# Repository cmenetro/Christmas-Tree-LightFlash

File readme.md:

Christmas Tree Light Flash
===

The way to blink a christmas light who is powered on batteries.
For blink I use a 555 timer chip.

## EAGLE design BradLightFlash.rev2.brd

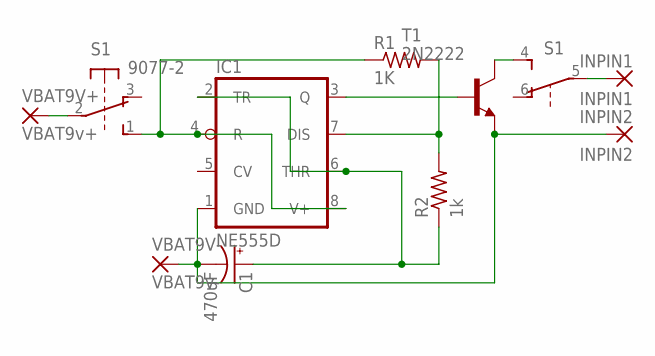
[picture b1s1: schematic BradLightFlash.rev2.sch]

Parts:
C1: 470uF; E2,5-6
IC1: NE555D; SO08
INPIN1: INPIN1; 2,54/1,1
INPIN2: INPIN2; 2,54/1,1
R1: 1K; 0309V
R2: 1k; 0309V
S1: 9077-2
T1: 2N2222; TO92-EBC-OVAL
VBAT9V+: VBAT9v+; 2,54/1,1
VBAT9V-: VBAT9v-; 2,54/1,1

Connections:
unnamed: S1.2, VBAT9V+.1
unnamed: IC1.4 (R), IC1.8 (V+), R1.1, S1.1 (S)
unnamed: C1.-, IC1.1 (GND), INPIN2.1, T1.E, VBAT9V-.1
unnamed: C1.+, IC1.2 (TR), IC1.6 (THR), R2.1
unnamed: IC1.7 (DIS), R1.2, R2.2
unnamed: IC1.3 (Q), T1.B
unnamed: S1.4 (S), T1.C
unnamed: INPIN1.1, S1.5

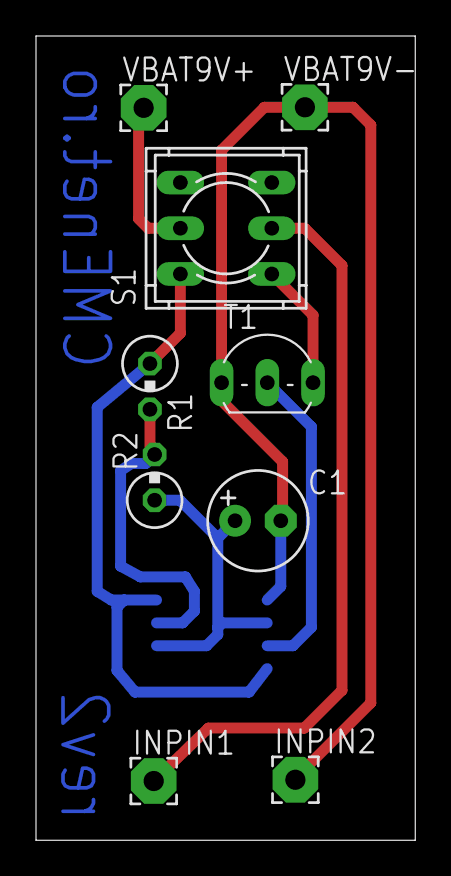
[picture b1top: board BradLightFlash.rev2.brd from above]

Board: 2 copper layers, 21.1 x 44.7 mm, 10 parts (1 on the bottom side), 8 nets.

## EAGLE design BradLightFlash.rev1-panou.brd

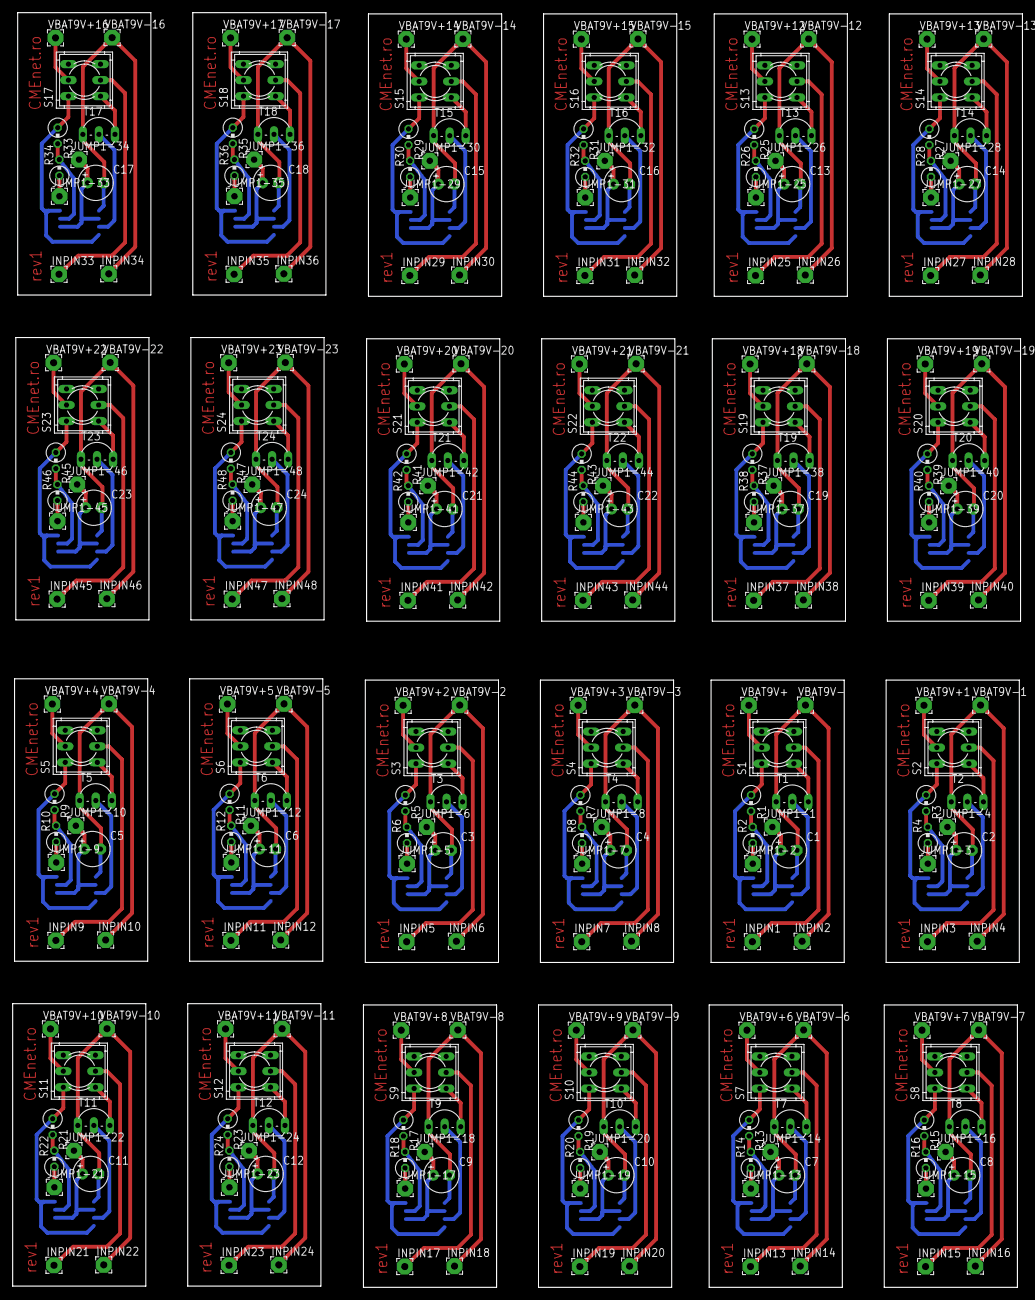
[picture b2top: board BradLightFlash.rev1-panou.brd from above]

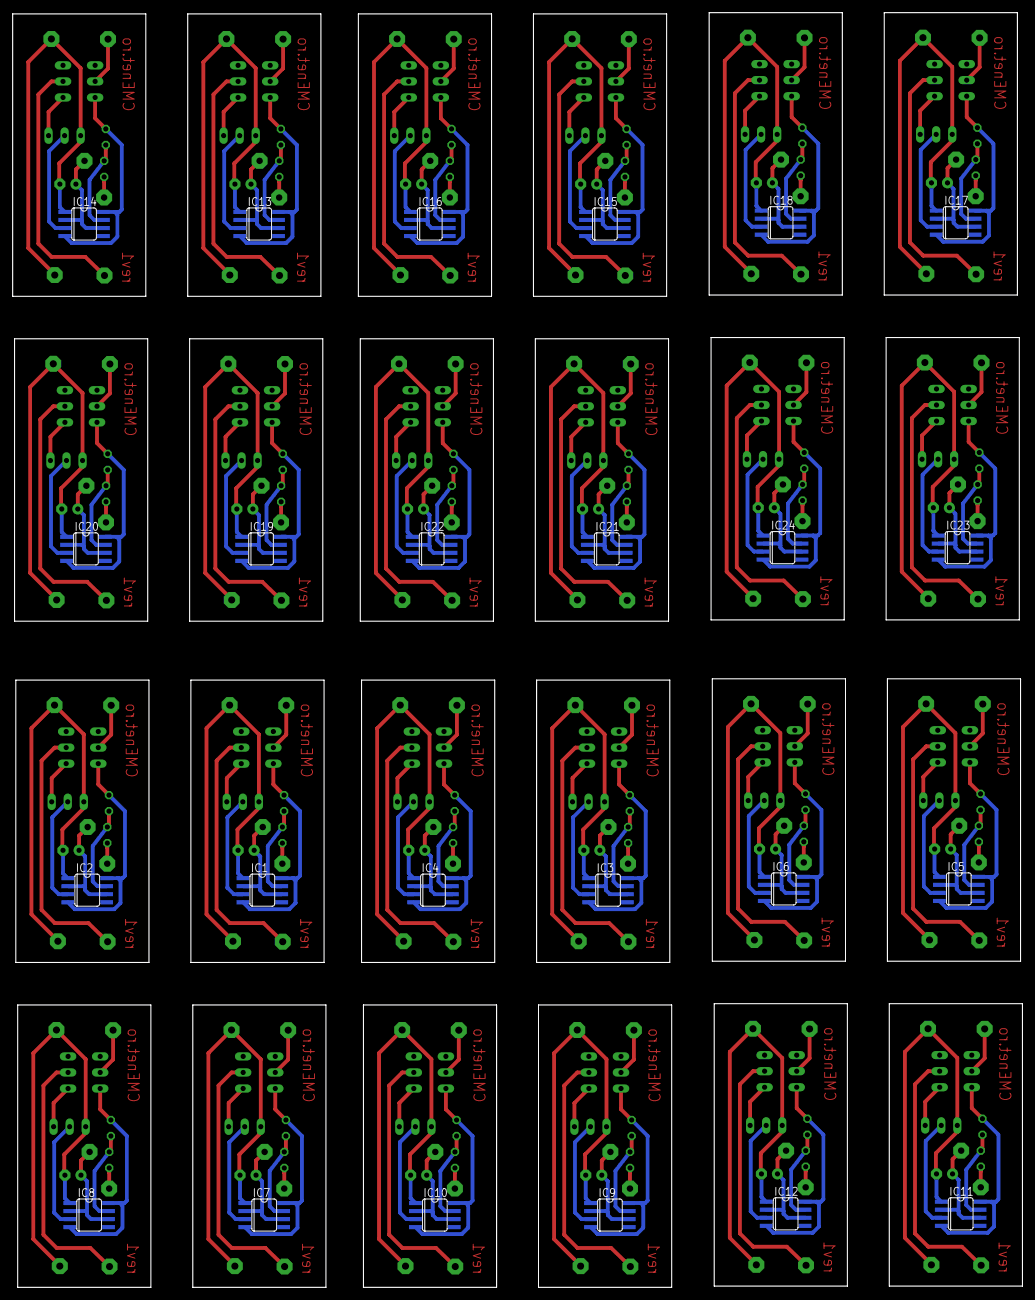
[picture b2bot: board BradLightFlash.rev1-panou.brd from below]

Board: 2 copper layers, 159.8 x 201.7 mm, 288 parts (24 on the bottom side), 216 nets.

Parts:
C1, C2, C3, C4, C5, C6, C7, C8, C9, C10, C11, C12, C13, C14, C15, C16, C17, C18, C19, C20, C21, C22, C23, C24: 470uF; E2,5-6
IC1, IC2, IC3, IC4, IC5, IC6, IC7, IC8, IC9, IC10, IC11, IC12, IC13, IC14, IC15, IC16, IC17, IC18, IC19, IC20, IC21, IC22, IC23, IC24: NE555D; SO08
INPIN1, INPIN3, INPIN5, INPIN7, INPIN9, INPIN11, INPIN13, INPIN15, INPIN17, INPIN19, INPIN21, INPIN23, INPIN25, INPIN27, INPIN29, INPIN31, INPIN33, INPIN35, INPIN37, INPIN39, INPIN41, INPIN43, INPIN45, INPIN47: INPIN1; 2,54/1,1
INPIN2, INPIN4, INPIN6, INPIN8, INPIN10, INPIN12, INPIN14, INPIN16, INPIN18, INPIN20, INPIN22, INPIN24, INPIN26, INPIN28, INPIN30, INPIN32, INPIN34, INPIN36, INPIN38, INPIN40, INPIN42, INPIN44, INPIN46, INPIN48: INPIN2; 2,54/1,1
JUMP1-1, JUMP1-2, JUMP1-3, JUMP1-4, JUMP1-5, JUMP1-6, JUMP1-7, JUMP1-8, JUMP1-9, JUMP1-10, JUMP1-11, JUMP1-12, JUMP1-13, JUMP1-14, JUMP1-15, JUMP1-16, JUMP1-17, JUMP1-18, JUMP1-19, JUMP1-20, JUMP1-21, JUMP1-22, JUMP1-23, JUMP1-24, JUMP1-25, JUMP1-26, JUMP1-27, JUMP1-28, JUMP1-29, JUMP1-30, JUMP1-31, JUMP1-32, JUMP1-33, JUMP1-34, JUMP1-35, JUMP1-36, JUMP1-37, JUMP1-38, JUMP1-39, JUMP1-40, JUMP1-41, JUMP1-42, JUMP1-43, JUMP1-44, JUMP1-45, JUMP1-46, JUMP1-47, JUMP1-48: 2,54/1,0
R1, R3, R5, R7, R9, R11, R13, R15, R17, R19, R21, R23, R25, R27, R29, R31, R33, R35, R37, R39, R41, R43, R45, R47: 1K; 0309V
R2, R4, R6, R8, R10, R12, R14, R16, R18, R20, R22, R24, R26, R28, R30, R32, R34, R36, R38, R40, R42, R44, R46, R48: 1k; 0309V
S1, S2, S3, S4, S5, S6, S7, S8, S9, S10, S11, S12, S13, S14, S15, S16, S17, S18, S19, S20, S21, S22, S23, S24: 9077-2
T1, T2, T3, T4, T5, T6, T7, T8, T9, T10, T11, T12, T13, T14, T15, T16, T17, T18, T19, T20, T21, T22, T23, T24: 2N2222; TO92-EBC-OVAL
VBAT9V+, VBAT9V+1, VBAT9V+2, VBAT9V+3, VBAT9V+4, VBAT9V+5, VBAT9V+6, VBAT9V+7, VBAT9V+8, VBAT9V+9, VBAT9V+10, VBAT9V+11, VBAT9V+12, VBAT9V+13, VBAT9V+14, VBAT9V+15, VBAT9V+16, VBAT9V+17, VBAT9V+18, VBAT9V+19, VBAT9V+20, VBAT9V+21, VBAT9V+22, VBAT9V+23: VBAT9v+; 2,54/1,1
VBAT9V-, VBAT9V-1, VBAT9V-2, VBAT9V-3, VBAT9V-4, VBAT9V-5, VBAT9V-6, VBAT9V-7, VBAT9V-8, VBAT9V-9, VBAT9V-10, VBAT9V-11, VBAT9V-12, VBAT9V-13, VBAT9V-14, VBAT9V-15, VBAT9V-16, VBAT9V-17, VBAT9V-18, VBAT9V-19, VBAT9V-20, VBAT9V-21, VBAT9V-22, VBAT9V-23: VBAT9v-; 2,54/1,1

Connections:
unnamed: S1.2, VBAT9V+.1
unnamed: IC1.4, IC1.8, R1.1, S1.1
unnamed: C1.-, IC1.1, INPIN2.1, T1.E, VBAT9V-.1
unnamed: C1.+, IC1.2, IC1.6, JUMP1-1.1
unnamed: JUMP1-2.1, R2.1
unnamed: IC1.7, R1.2, R2.2
unnamed: IC1.3, T1.B
unnamed: S1.4, T1.C
unnamed: S2.2, VBAT9V+1.1
unnamed: INPIN1.1, S1.5
unnamed: IC2.4, IC2.8, R3.1, S2.1
unnamed: C2.-, IC2.1, INPIN4.1, T2.E, VBAT9V-1.1
unnamed: C2.+, IC2.2, IC2.6, JUMP1-4.1
unnamed: IC2.7, R3.2, R4.2
unnamed: IC2.3, T2.B
unnamed: S2.4, T2.C
unnamed: INPIN3.1, S2.5
unnamed: JUMP1-3.1, R4.1
unnamed: S3.2, VBAT9V+2.1
unnamed: IC3.4, IC3.8, R5.1, S3.1
unnamed: C3.-, IC3.1, INPIN6.1, T3.E, VBAT9V-2.1
unnamed: C3.+, IC3.2, IC3.6, JUMP1-6.1
unnamed: IC3.7, R5.2, R6.2
unnamed: IC3.3, T3.B
unnamed: S3.4, T3.C
unnamed: INPIN5.1, S3.5
unnamed: JUMP1-5.1, R6.1
unnamed: S4.2, VBAT9V+3.1
unnamed: IC4.4, IC4.8, R7.1, S4.1
unnamed: C4.-, IC4.1, INPIN8.1, T4.E, VBAT9V-3.1
unnamed: C4.+, IC4.2, IC4.6, JUMP1-8.1
unnamed: IC4.7, R7.2, R8.2
unnamed: IC4.3, T4.B
unnamed: S4.4, T4.C
unnamed: INPIN7.1, S4.5
unnamed: JUMP1-7.1, R8.1
unnamed: S5.2, VBAT9V+4.1
unnamed: IC5.4, IC5.8, R9.1, S5.1
unnamed: C5.-, IC5.1, INPIN10.1, T5.E, VBAT9V-4.1
unnamed: C5.+, IC5.2, IC5.6, JUMP1-10.1
unnamed: IC5.7, R9.2, R10.2
unnamed: IC5.3, T5.B
unnamed: S5.4, T5.C
unnamed: INPIN9.1, S5.5
unnamed: JUMP1-9.1, R10.1
unnamed: S6.2, VBAT9V+5.1
unnamed: IC6.4, IC6.8, R11.1, S6.1
unnamed: C6.-, IC6.1, INPIN12.1, T6.E, VBAT9V-5.1
unnamed: C6.+, IC6.2, IC6.6, JUMP1-12.1
unnamed: IC6.7, R11.2, R12.2
unnamed: IC6.3, T6.B
unnamed: S6.4, T6.C
unnamed: INPIN11.1, S6.5
unnamed: JUMP1-11.1, R12.1
unnamed: S7.2, VBAT9V+6.1
unnamed: IC7.4, IC7.8, R13.1, S7.1
unnamed: C7.-, IC7.1, INPIN14.1, T7.E, VBAT9V-6.1
unnamed: C7.+, IC7.2, IC7.6, JUMP1-14.1
unnamed: IC7.7, R13.2, R14.2
unnamed: IC7.3, T7.B
unnamed: S7.4, T7.C
unnamed: INPIN13.1, S7.5
unnamed: JUMP1-13.1, R14.1
unnamed: S8.2, VBAT9V+7.1
unnamed: IC8.4, IC8.8, R15.1, S8.1
unnamed: C8.-, IC8.1, INPIN16.1, T8.E, VBAT9V-7.1
unnamed: C8.+, IC8.2, IC8.6, JUMP1-16.1
unnamed: IC8.7, R15.2, R16.2
unnamed: IC8.3, T8.B
unnamed: S8.4, T8.C
unnamed: INPIN15.1, S8.5
unnamed: JUMP1-15.1, R16.1
unnamed: S9.2, VBAT9V+8.1
unnamed: IC9.4, IC9.8, R17.1, S9.1
unnamed: C9.-, IC9.1, INPIN18.1, T9.E, VBAT9V-8.1
unnamed: C9.+, IC9.2, IC9.6, JUMP1-18.1
unnamed: IC9.7, R17.2, R18.2
unnamed: IC9.3, T9.B
unnamed: S9.4, T9.C
unnamed: INPIN17.1, S9.5
unnamed: JUMP1-17.1, R18.1
unnamed: S10.2, VBAT9V+9.1
unnamed: IC10.4, IC10.8, R19.1, S10.1
unnamed: C10.-, IC10.1, INPIN20.1, T10.E, VBAT9V-9.1
unnamed: C10.+, IC10.2, IC10.6, JUMP1-20.1
unnamed: IC10.7, R19.2, R20.2
unnamed: IC10.3, T10.B
unnamed: S10.4, T10.C
unnamed: INPIN19.1, S10.5
unnamed: JUMP1-19.1, R20.1
unnamed: S11.2, VBAT9V+10.1
unnamed: IC11.4, IC11.8, R21.1, S11.1
unnamed: C11.-, IC11.1, INPIN22.1, T11.E, VBAT9V-10.1
unnamed: C11.+, IC11.2, IC11.6, JUMP1-22.1
unnamed: IC11.7, R21.2, R22.2
unnamed: IC11.3, T11.B
unnamed: S11.4, T11.C
unnamed: INPIN21.1, S11.5
unnamed: JUMP1-21.1, R22.1
unnamed: S12.2, VBAT9V+11.1
unnamed: IC12.4, IC12.8, R23.1, S12.1
unnamed: C12.-, IC12.1, INPIN24.1, T12.E, VBAT9V-11.1
unnamed: C12.+, IC12.2, IC12.6, JUMP1-24.1
unnamed: IC12.7, R23.2, R24.2
unnamed: IC12.3, T12.B
unnamed: S12.4, T12.C
unnamed: INPIN23.1, S12.5
unnamed: JUMP1-23.1, R24.1
unnamed: S13.2, VBAT9V+12.1
unnamed: IC13.4, IC13.8, R25.1, S13.1
unnamed: C13.-, IC13.1, INPIN26.1, T13.E, VBAT9V-12.1
unnamed: C13.+, IC13.2, IC13.6, JUMP1-26.1
unnamed: IC13.7, R25.2, R26.2
unnamed: IC13.3, T13.B
unnamed: S13.4, T13.C
unnamed: INPIN25.1, S13.5
unnamed: JUMP1-25.1, R26.1
unnamed: S14.2, VBAT9V+13.1
unnamed: IC14.4, IC14.8, R27.1, S14.1
unnamed: C14.-, IC14.1, INPIN28.1, T14.E, VBAT9V-13.1
unnamed: C14.+, IC14.2, IC14.6, JUMP1-28.1
unnamed: IC14.7, R27.2, R28.2
unnamed: IC14.3, T14.B
unnamed: S14.4, T14.C
unnamed: INPIN27.1, S14.5
unnamed: JUMP1-27.1, R28.1
unnamed: S15.2, VBAT9V+14.1
unnamed: IC15.4, IC15.8, R29.1, S15.1
unnamed: C15.-, IC15.1, INPIN30.1, T15.E, VBAT9V-14.1
unnamed: C15.+, IC15.2, IC15.6, JUMP1-30.1
unnamed: IC15.7, R29.2, R30.2
unnamed: IC15.3, T15.B
unnamed: S15.4, T15.C
unnamed: INPIN29.1, S15.5
unnamed: JUMP1-29.1, R30.1
unnamed: S16.2, VBAT9V+15.1
unnamed: IC16.4, IC16.8, R31.1, S16.1
unnamed: C16.-, IC16.1, INPIN32.1, T16.E, VBAT9V-15.1
unnamed: C16.+, IC16.2, IC16.6, JUMP1-32.1
unnamed: IC16.7, R31.2, R32.2
unnamed: IC16.3, T16.B
unnamed: S16.4, T16.C
unnamed: INPIN31.1, S16.5
unnamed: JUMP1-31.1, R32.1
unnamed: S17.2, VBAT9V+16.1
unnamed: IC17.4, IC17.8, R33.1, S17.1
unnamed: C17.-, IC17.1, INPIN34.1, T17.E, VBAT9V-16.1
unnamed: C17.+, IC17.2, IC17.6, JUMP1-34.1
unnamed: IC17.7, R33.2, R34.2
unnamed: IC17.3, T17.B
unnamed: S17.4, T17.C
unnamed: INPIN33.1, S17.5
unnamed: JUMP1-33.1, R34.1
unnamed: S18.2, VBAT9V+17.1
unnamed: IC18.4, IC18.8, R35.1, S18.1
unnamed: C18.-, IC18.1, INPIN36.1, T18.E, VBAT9V-17.1
unnamed: C18.+, IC18.2, IC18.6, JUMP1-36.1
unnamed: IC18.7, R35.2, R36.2
unnamed: IC18.3, T18.B
unnamed: S18.4, T18.C
unnamed: INPIN35.1, S18.5
unnamed: JUMP1-35.1, R36.1
unnamed: S19.2, VBAT9V+18.1
unnamed: IC19.4, IC19.8, R37.1, S19.1
unnamed: C19.-, IC19.1, INPIN38.1, T19.E, VBAT9V-18.1
unnamed: C19.+, IC19.2, IC19.6, JUMP1-38.1
unnamed: IC19.7, R37.2, R38.2
unnamed: IC19.3, T19.B
unnamed: S19.4, T19.C
unnamed: INPIN37.1, S19.5
unnamed: JUMP1-37.1, R38.1
unnamed: S20.2, VBAT9V+19.1
unnamed: IC20.4, IC20.8, R39.1, S20.1
unnamed: C20.-, IC20.1, INPIN40.1, T20.E, VBAT9V-19.1
unnamed: C20.+, IC20.2, IC20.6, JUMP1-40.1
unnamed: IC20.7, R39.2, R40.2
unnamed: IC20.3, T20.B
unnamed: S20.4, T20.C
unnamed: INPIN39.1, S20.5
unnamed: JUMP1-39.1, R40.1
unnamed: S21.2, VBAT9V+20.1
unnamed: IC21.4, IC21.8, R41.1, S21.1
unnamed: C21.-, IC21.1, INPIN42.1, T21.E, VBAT9V-20.1
unnamed: C21.+, IC21.2, IC21.6, JUMP1-42.1
unnamed: IC21.7, R41.2, R42.2
unnamed: IC21.3, T21.B
unnamed: S21.4, T21.C
unnamed: INPIN41.1, S21.5
unnamed: JUMP1-41.1, R42.1
unnamed: S22.2, VBAT9V+21.1
unnamed: IC22.4, IC22.8, R43.1, S22.1
unnamed: C22.-, IC22.1, INPIN44.1, T22.E, VBAT9V-21.1
unnamed: C22.+, IC22.2, IC22.6, JUMP1-44.1
unnamed: IC22.7, R43.2, R44.2
unnamed: IC22.3, T22.B
unnamed: S22.4, T22.C
unnamed: INPIN43.1, S22.5
unnamed: JUMP1-43.1, R44.1
unnamed: S23.2, VBAT9V+22.1
unnamed: IC23.4, IC23.8, R45.1, S23.1
unnamed: C23.-, IC23.1, INPIN46.1, T23.E, VBAT9V-22.1
unnamed: C23.+, IC23.2, IC23.6, JUMP1-46.1
unnamed: IC23.7, R45.2, R46.2
unnamed: IC23.3, T23.B
unnamed: S23.4, T23.C
unnamed: INPIN45.1, S23.5
unnamed: JUMP1-45.1, R46.1
unnamed: S24.2, VBAT9V+23.1
unnamed: IC24.4, IC24.8, R47.1, S24.1
unnamed: C24.-, IC24.1, INPIN48.1, T24.E, VBAT9V-23.1
unnamed: C24.+, IC24.2, IC24.6, JUMP1-48.1
unnamed: IC24.7, R47.2, R48.2
unnamed: IC24.3, T24.B
unnamed: S24.4, T24.C
unnamed: INPIN47.1, S24.5
unnamed: JUMP1-47.1, R48.1

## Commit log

2014-12-20 :confetti_ball: Added .gitattributes & .gitignore files
